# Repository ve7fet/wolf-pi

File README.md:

# wolf-pi

## What is it?
A carrier board for the NanoPi Duo 2 supporting Direwolf and other amateur radio applications. 
See http://wiki.friendlyarm.com/wiki/index.php/NanoPi_Duo2 for details on the NanoPi Duo 2. Schematics of the NanoPi Duo 2 and it's 
factory carrier board schematic are in the [docs](./docs) folder.

The NanoPi Duo 2 has a built-in sound card (ADC/DAC), GPIO, WiFi, and Ethernet, making it an attractive product for integration.

This device allows you to use a NanoPi Duo 2 with the Direwolf Project. See https://packet-radio.net/direwolf/

## Implementation
In this application, we wire out the Ethernet (following the design used on the NanoPi IoT carrier board), as that is often preferred 
in a stand-alone application, for connection to a LAN.

The GPIO is used with the built-in functions in Direwolf for /PTT and software indication of Carrier Detect.

A 555-based (selectable) time-out-timer is employed, to prevent a locked-up transmitter or software from holding up the radio channel
with dead carrier. This circuit is based on the one recommended in the Direwolf documentation.

For telemetry applications, support for the ADS1115 ADC converter is included. This is accomplished by using a commonly available 
breakout board from Sparkfun/Adafruit/Universal Solder. The header pins for the breakout solder directly on to the carrier.

Non-populated resistor positions are provided for build-your-own voltage dividers for making single-ended ADC measurements (battery voltages, door switches, etc.).

JP2 is provided to facilitate easy measurement of the battery voltage on ADC AN0.

Support for Dallas 1-wire sensors is provided, with pads available to install a DS18B20 on-board, if desired. Note that the onboard DS18B20 will be measuring the temperature inside the enclosure...

ADC and 1-Wire are wired out to a header connector that is external to the case, for external connections.

The DB9 connector is wired to be compatible with Kantronics KPC3+ cables. Additional solder jumpers are provided to modify some of those pin functions for custom applications.

Additional GPIO (buffered) outputs are also added for future use.

Support for hardware COS (DCD) is provided for future applications.

Ferrite beads are used to reduce RFI/EMI.

The board is designed to be installed in a Hammond 1455K1201 case. Actually, it will fit the 1455J1201 (which is thinner). The -1202 version is less expensive (plastic end panels, vs aluminum ones), if you are going to be replacing the end panels with laser cut ones. End plates are still to be designed.

Alternatively, an enclosure has been designed in FreeCad, with the .stl [files available](./enclosure). Confirmed working for the v1.2 board, printed in PLA. Uses #4-40 hardware.

## Usage
The easiest way to get going is to install an [Armbian](https://armbian.com) image, using their imager.

As of 2026/09/03, it was installing:

*v26.11 rolling for NanoPi Duo2 running Armbian Linux 6.18.48-current-sunxi*

### Boot Configuration Changes
In order to utilize all the features of the implementation, additional configuration of the Armbian environment is required.

The following changes are needed to `/boot/armbianEnv.txt` in order to enable the sound card (codec), 1-wire, and i2c (for the ADS1115).

```
overlays=analog-codec i2c0 usbhost0 usbhost2 usbhost3 w1-gpio
param_w1_pin=PA13
param_w1_pin_int_pullup=0
```

### 1-Wire
With the changes to `/boot/armbianEnv.txt`, the 1-wire subsystem will be available in `/sys/bus/w1/devices`.

If the onboard sensor is installed, it should enumerate with a `28-` prefix.

Follow any of the many sources on the Internet for how to utilize it from there.

### ADC via i2c
With the changes to `/boot/armbianEnv.txt`, the ADS1115 daughter board should be detected. 

Install the i2c tools:

```
sudo apt install i2c-tools -y
```

Make sure the bus is there:

```
ve7fet@nanopiduo2:~$ ls /dev/i2c*
/dev/i2c-0
```

Make sure we can see the ADC at address 0x48:

```
ve7fet@nanopiduo2:~$ sudo i2cdetect -y 0
     0  1  2  3  4  5  6  7  8  9  a  b  c  d  e  f
00:                         -- -- -- -- -- -- -- --
10: -- -- -- -- -- -- -- -- -- -- -- -- -- -- -- --
20: -- -- -- -- -- -- -- -- -- -- -- -- -- -- -- --
30: -- -- -- -- -- -- -- -- -- -- -- -- -- -- -- --
40: -- -- -- -- -- -- -- -- 48 -- -- -- -- -- -- --
50: -- -- -- -- -- -- -- -- -- -- -- -- -- -- -- --
60: -- -- -- -- -- -- -- -- -- -- -- -- -- -- -- --
70: -- -- -- -- -- -- -- --
```

Unfortunately, the Armbian kernel doesn't have the driver compiled into it in order to use userspace tools. So, that means one will have to access it directly via i2c.

With a little massaging, the library from https://github.com/sanjuruk/ADS1X15_TLA2024_Linux is capable of accessing the ADC.

Note that the value returned by the "single ended" utility is the ADC count. In order to convert it back to a voltage, you'd need to do something like:

```
#include <cstdio>
#include <unistd.h>
#include "ADS1X15_TLA2024.h"

ADS1115 ads;  /* Use this for the 16-bit version */
// ADS1015 ads;     /* Use this for the 12-bit version */
// TLA2024 ads;

int DEBUG = 1;
float AIN0vout, AIN1vout, AIN2vout, AIN3vout;
float AIN0cal, AIN1cal, AIN2cal, AIN3cal;
float PGA = 4.096; /* PGA is defined by GAIN setting */

// AIN0 Resistors
float R5 = 10000; // 10k ohms
float R6 = 3000;  // 3k ohms
// AIN1 Resistors
float R7 = 1; // dummy, so we don't divide by 0
float R8 = 1; // dummy, so we don't divide by 0
// AIN2 Resistors
float R9 = 1000; // 1kohm
float R10 = 3740; // 3.74kohm
// AIN3 Resistors
float R12 = 1;
float R13 = 1;

// AIN0 Max Input Voltage
//
// VINmax = (VDD + 0.3) x ((R5 + R6)/R6)
// VINmax = (3.6) x ((13000)/3000)
// VINmax = 15.6VDC
//
// AIN2 Max Input Voltage
//
// VINmax = (VDD + 0.3) x ((R9 + R10)/R10)
// VINmax = (3.6) x ((4740)/3740)
// VINmax = 4.56VDC

int main()
{
    int16_t adc[4];
    int8_t i;

    if (DEBUG) {
        printf("Getting single-ended readings from AIN0..3\n");
        printf("ADC Range: +/- 4.096V (1 bit = 2mV/ADS1015, 0.125mV/ADS1115)\n");
        printf("ADC Max Input: VDD + 0.3 = 3.6VDC\n\n");
    }

  // The ADC input range (or gain) can be changed via the following
  // functions, but be careful never to exceed VDD +0.3V max, or to
  // exceed the upper and lower limits if you adjust the input range!
  // Setting these values incorrectly may destroy your ADC!
  //                                                                ADS1015  ADS1115
  //                                                                -------  -------
  // ads.setGain(GAIN_TWOTHIRDS);  // 2/3x gain +/- 6.144V  1 bit = 3mV      0.1875mV (default)
  //
  // We're using VDD = 3.3V, so we will use GAIN_ONE to get the most resolution, being
  // careful to choose our voltage divider resistors!
    ads.setGain(GAIN_ONE);        // 1x gain   +/- 4.096V  1 bit = 2mV      0.125mV
  // ads.setGain(GAIN_TWO);        // 2x gain   +/- 2.048V  1 bit = 1mV      0.0625mV
  // ads.setGain(GAIN_FOUR);       // 4x gain   +/- 1.024V  1 bit = 0.5mV    0.03125mV
  // ads.setGain(GAIN_EIGHT);      // 8x gain   +/- 0.512V  1 bit = 0.25mV   0.015625mV
  // ads.setGain(GAIN_SIXTEEN);    // 16x gain  +/- 0.256V  1 bit = 0.125mV  0.0078125mV

    for (i = 0; i < 4; i++) {
        adc[i] = ads.readADC_SingleEnded(i);
        if (DEBUG) {
            printf("AIN%i: %d\n", i, adc[i]);
        }
    }

    /* Calculate output voltage for AIN0. */
    AIN0vout = (adc[0]*(PGA/32767))*((R5+R6)/R6);
    printf("AIN0vout = %.2f\n", AIN0vout);

    /* Calculate output voltage for AIN1. */
    AIN1vout = (adc[1]*(PGA/32767))*((R7+R8)/R8);
    printf("AIN1vout = %.2f\n", AIN1vout);

    /* Calculate output voltage for AIN2. */
    AIN2vout = (adc[2]*(PGA/32767))*((R9+R10)/R10);
    printf("AIN2vout = %.2f\n", AIN2vout);

    /* Calculate output voltage for AIN3. */
    AIN3vout = (adc[3]*(PGA/32767))*((R12+R13)/R13);
    printf("AIN3vout = %.2f\n", AIN3vout);
```
See https://github.com/ve7fet/wolfpiADC for the full library.

### Sound Card
You can use `alsamixer` to set the audio levels. Use `sudo alsactl store` to save settings in `/var/lib/alsa/asound.state` (*remember to backup this file*).

If you run Direwolf out of the box, it will likely complain:

```
Audio input device 0 error code -5: Input/output error
```

That is because there is no capture device selected. You can either run this:

```
#mic1 CAPTURE switch (on/off) - this will let you use the microphone
/usr/bin/amixer -c 0 cset numid=18 on
```

Or, load `alsamixer`, and select MIC1 as the capture device.

### GPIO
We use GPIO for the /PTT (signal and LED), and the DCD LED.

Put the following in the `direwolf.conf` for Channel 0 to enable them:

```
MODEM 1200

# Our PTT is on GPIOL11 (Pin 9)
PTT GPIO 363
# Our DCD LED is on GPIOG11 (Pin 11)
DCD GPIO 203
```

Note that this is the deprecated sysfs way of using the GPIOs... but it works, for now.

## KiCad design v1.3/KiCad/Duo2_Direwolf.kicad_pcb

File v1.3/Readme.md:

This version makes the following changes from v1.2:

- Fix C14/C20 Silkscreen. 
- Change solder jumpers to open. YOU NEED TO SOLDER THE OPTIONS YOU WANT DURING ASSEMBLY.
- Change TOT jumper to solder type instead of pin header. 
- Change DB9 mounting holes to plated/GND. 
- Move ETH jack outward.
- Move C11, D3, JP6.
- Correct R11/C9/U1 connections for TOT
- Update value of R6 to increase Vmax for AIN0 from 13.2V to 15.6V

This version has NOT been manufactured (yet) to verify operation.

Project/Schematic/Board saved with KiCad V9.04. DRC needs to be re-run, errors/warnings addressed, 
and Gerbers re-exported (existing Gerbers have been removed, as they are no longer valid).

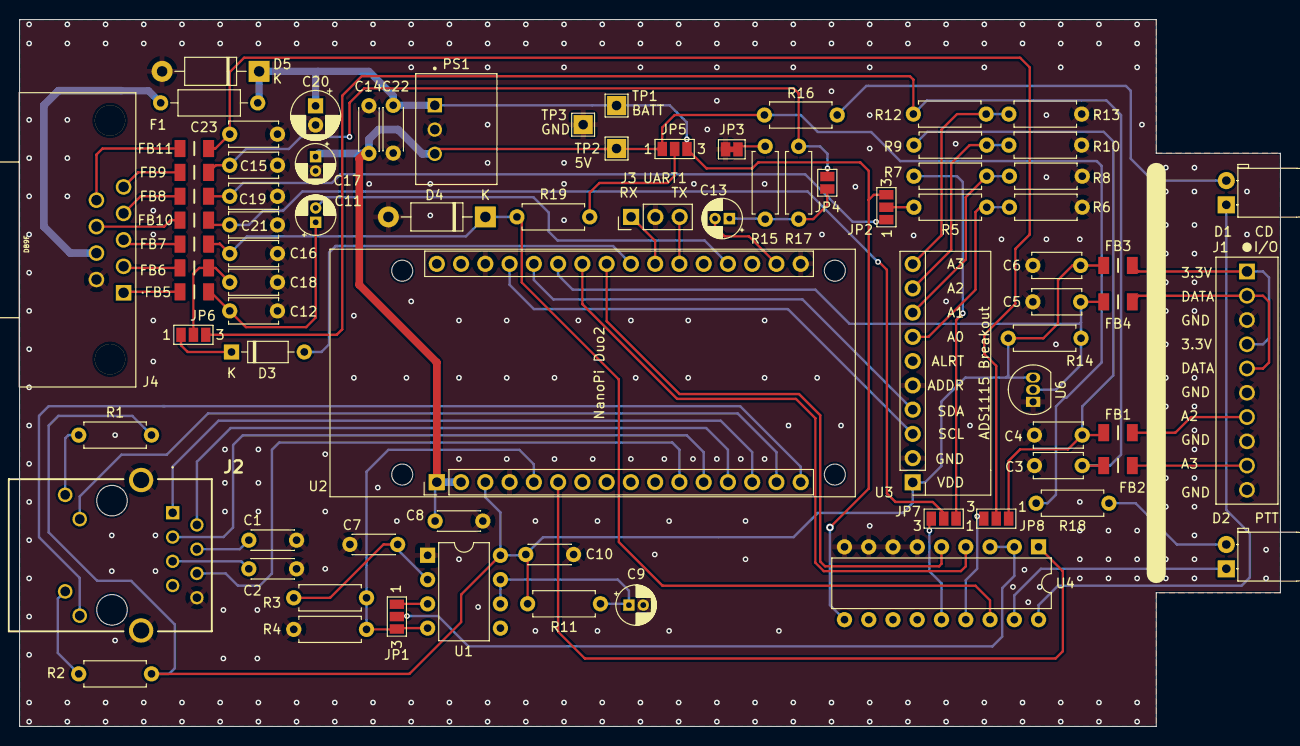
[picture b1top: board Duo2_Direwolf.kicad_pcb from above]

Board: 2 copper layers, 132.0 x 74.0 mm, 80 parts (0 on the bottom side), 67 nets.

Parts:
C1, C2, C7, C8, C10, C14, C22: 0.1uF; C_Disc_D4.3mm_W1.9mm_P5.00mm
C3, C4, C5, C6, C12, C15, C16, C18, C19, C21, C23: 47pF; C_Disc_D5.0mm_W2.5mm_P5.00mm
C9, C11, C13, C17: 10uF; CP_Radial_D4.0mm_P1.50mm
C20: 1uF; CP_Radial_D5.0mm_P2.00mm
D1: CD; LED_D5.0mm_Horizontal_O1.27mm_Z3.0mm
D2: PTT; LED_D5.0mm_Horizontal_O1.27mm_Z3.0mm
D3: 1N914; D_DO-35_SOD27_P7.62mm_Horizontal
D4, D5: 1N4001; D_DO-41_SOD81_P10.16mm_Horizontal
F1: 1A; R_Axial_DIN0207_L6.3mm_D2.5mm_P10.16mm_Horizontal
FB1, FB2, FB3, FB4, FB5, FB6, FB7, FB8, FB9, FB10, FB11: MH3261-601Y; BEADC3216X130N
J1: I/O; TE_1-282834-0
J2: ARJM11A3-009-AB-ER2-T; ARJM11A3009ABER2T
J3: UART1; PinHeader_1x03_P2.54mm_Vertical
J4: DB9F; TE_2311765-1
JP1: TOT Select; SolderJumper-3_P1.3mm_Open_Pad1.0x1.5mm_NumberLabels
JP2: EXT/BATT SEL; SolderJumper-3_P1.3mm_Open_Pad1.0x1.5mm_NumberLabels
JP3: Pad Bypass; SolderJumper-2_P1.3mm_Bridged_Pad1.0x1.5mm
JP4: Pad Bypass; SolderJumper-2_P1.3mm_Open_Pad1.0x1.5mm
JP5: Pullup; SolderJumper-3_P1.3mm_Open_Pad1.0x1.5mm_NumberLabels
JP6: COS/A3 SEL; SolderJumper-3_P1.3mm_Open_Pad1.0x1.5mm_NumberLabels
JP7: AN1/GPIOA16 SEL; SolderJumper-3_P1.3mm_Open_Pad1.0x1.5mm_NumberLabels
JP8: AN2/GPIOA14 SEL; SolderJumper-3_P1.3mm_Open_Pad1.0x1.5mm_NumberLabels
PS1: R-78E5.0-1.0; CONV_R-78E5.0-1.0
R1, R2: 330; R_Axial_DIN0207_L6.3mm_D2.5mm_P7.62mm_Horizontal
R3, R19: 10k; R_Axial_DIN0207_L6.3mm_D2.5mm_P7.62mm_Horizontal
R4: 100k; R_Axial_DIN0207_L6.3mm_D2.5mm_P7.62mm_Horizontal
R5: 10K; R_Axial_DIN0207_L6.3mm_D2.5mm_P7.62mm_Horizontal
R6: 3.00k; R_Axial_DIN0207_L6.3mm_D2.5mm_P7.62mm_Horizontal
R7, R8, R9, R10, R12, R13: NP; R_Axial_DIN0207_L6.3mm_D2.5mm_P7.62mm_Horizontal
R11: 1M; R_Axial_DIN0207_L6.3mm_D2.5mm_P7.62mm_Horizontal
R14: 4.7k; R_Axial_DIN0207_L6.3mm_D2.5mm_P7.62mm_Horizontal
R15: 68k; R_Axial_DIN0207_L6.3mm_D2.5mm_P7.62mm_Horizontal
R16, R18: 470; R_Axial_DIN0207_L6.3mm_D2.5mm_P7.62mm_Horizontal
R17: 470k; R_Axial_DIN0207_L6.3mm_D2.5mm_P7.62mm_Horizontal
TP1: BATT; TestPoint_THTPad_2.0x2.0mm_Drill1.0mm
TP2: 5V; TestPoint_THTPad_2.0x2.0mm_Drill1.0mm
TP3: GND; TestPoint_THTPad_2.0x2.0mm_Drill1.0mm
U1: LMC555xN; DIP-8_W7.62mm
U2: NanoPi_Duo2; NanoPi_Duo2_Foot
U3: ADS1115-Breakout; ADS1115 Breakout
U4: ULN2803A; DIP-18_W7.62mm
U6: DS18S20; TO-92_Inline

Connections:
+3V3: C6.1, C10.1, FB3.2, R1.2, R2.2, R11.1, R14.2, U1.8 (VCC), U2.5 (SYS_3.3V), U3.1 (VDD), U6.3 (VDD)
+5V: C8.1, C14.1, C17.1, JP5.1 (A), PS1.3 (+VOUT), R16.2, R18.2, TP2.1, U2.1 (VDD_5V), U2.3 (VDD_5V)
+BATT: C20.1, C22.1, D5.1 (K), F1.1, JP2.3 (B), JP5.3 (B), PS1.1 (+VIN), TP1.1, U4.10 (COM)
/1-Wire: C5.1, FB4.2, R14.1, U2.12 (UART3_TX/SPI1_CS/GPIOA13), U6.2 (DQ)
/AN0: C19.1, FB8.1, JP2.1 (A)
/AN1: JP7.1 (A), R7.2
/AN2: C4.1, FB1.2, JP8.1 (A), R9.2
/AN3: C3.1, FB2.2, JP6.3 (B), R12.2
/EXT PWR IN: F1.2, J4.7
/PTT: C16.1, D4.1 (K), FB7.1, R19.1, U4.16 (O3)
/RXA: C15.1, FB9.1, JP4.2 (B), R17.1
/TXA: C11.1, C12.1, FB5.1
GND: C1.1, C2.2, C3.2, C4.2, C5.2, C6.2, C7.2, C8.2, C9.2, C10.2, C12.2, C14.2, C15.2, C16.2, C17.2, C18.2, C19.2, C20.2, C21.2, C22.2, C23.2, D4.2 (A), D5.2 (A), J1.3, J1.6, J1.8, J1.10, J2.8 (GND), J2.MH1, J2.MH2, J3.2, J4.6, JP3.1 (A), PS1.2 (GND), R4.1, R6.1, R8.1, R10.1, R13.1, TP3.1, U1.1 (GND), U2.6 (GND), U2.7 (GND), U2.32 (MIC_N), U3.2 (GND), U3.5 (ADDR), U4.6 (I6), U4.7 (I7), U4.8 (I8), U4.9 (GND), U6.1 (GND)
unnamed: D1.2 (A), R16.1
unnamed: D1.1 (K), U4.18 (O1)
unnamed: D2.2 (A), R18.1
unnamed: D2.1 (K), U4.17 (O2)
unnamed: D3.2 (A), U2.18 (UART3_RTS/SPI1_MOSI/GPIOA15)
unnamed: D3.1 (K), JP6.1 (A)
unnamed: FB1.1, J1.7
unnamed: FB2.1, J1.9
unnamed: FB3.1, J1.1, J1.4
unnamed: FB4.1, J1.2, J1.5
unnamed: FB5.2, J4.1
unnamed: FB6.2, J4.2
unnamed: FB7.2, J4.3
unnamed: FB8.2, J4.4
unnamed: FB9.2, J4.5
unnamed: FB10.1, J4.8
unnamed: FB11.1, J4.9
unnamed: J2.9 (A_GREEN), R1.1
unnamed: J2.11 (A_YELLOW), R2.1
unnamed: C1.2, J2.4 (CT_1)
unnamed: C2.1, J2.5 (CT_2)
unnamed: J2.10 (K_GREEN), U2.29 (EPHY-LED-LINK)
unnamed: J2.12 (K_YELLOW), U2.31 (EPHY-LED-SPD)
unnamed: J2.3 (RD+), U2.23 (EPHY-RXP)
unnamed: J2.6 (RD-), U2.21 (EPHY-RXN)
unnamed: J2.1 (TD+), U2.27 (EPHY-TXP)
unnamed: J2.2 (TD-), U2.25 (EPHY-TXN)
unnamed: J3.1, U2.20 (UART1_RX/GPIOG7)
unnamed: J3.3, U2.22 (UART1_TX/GPIOG6)
unnamed: JP1.1 (A), U1.3 (Q)
unnamed: JP1.3 (B), R3.1, R4.2, U1.4 (R), U2.9 (GPIOL11/IR-RX)
unnamed: JP1.2 (C), U4.2 (I2), U4.3 (I3)
unnamed: JP2.2 (C), R5.2
unnamed: JP3.2 (B), R15.1
unnamed: C13.1, JP4.1 (A), R15.2, R17.2
unnamed: JP5.2 (C), R19.2
unnamed: C18.1, FB6.1, JP6.2 (C)
unnamed: JP7.3 (B), U4.14 (O5)
unnamed: C21.1, FB10.2, JP7.2 (C)
unnamed: JP8.3 (B), U4.15 (O4)
unnamed: C23.1, FB11.2, JP8.2 (C)
unnamed: C9.1, R11.2, U1.6 (THR), U1.7 (DIS)
unnamed: C7.1, R3.2, U1.2 (TR)
unnamed: U2.11 (GPIOG11), U4.1 (I1)
unnamed: U2.8 (I2C0_SCL/GPIOA11), U3.3 (SCL)
unnamed: U2.10 (I2C0_SDA/GPIOA12), U3.4 (SDA)
unnamed: C11.2, U2.26 (LINEOUT_L)
unnamed: C13.2, U2.30 (MIC_P)
unnamed: U2.16 (UART3_CTS/SPI1_MISO/GPIOA16), U4.5 (I5)
unnamed: U2.14 (UART3_RX/SPI1_CLK/GPIOA14), U4.4 (I4)
unnamed: R5.1, R6.2, U3.7 (A0)
unnamed: R7.1, R8.2, U3.8 (A1)
unnamed: R9.1, R10.2, U3.9 (A2)
unnamed: R12.1, R13.2, U3.10 (A3)

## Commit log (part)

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2022-02-05 Rename Read.md to Readme.md
2022-02-05 Upload v1.2 files.
2022-02-05 Add BOM.
2022-02-06 Add v1.3 files.
2022-02-06 Add v1.3 Gerbers.
2022-02-06 Update suitable enclosures.
2022-02-06 Spec sheets for the Hammond boxes.
